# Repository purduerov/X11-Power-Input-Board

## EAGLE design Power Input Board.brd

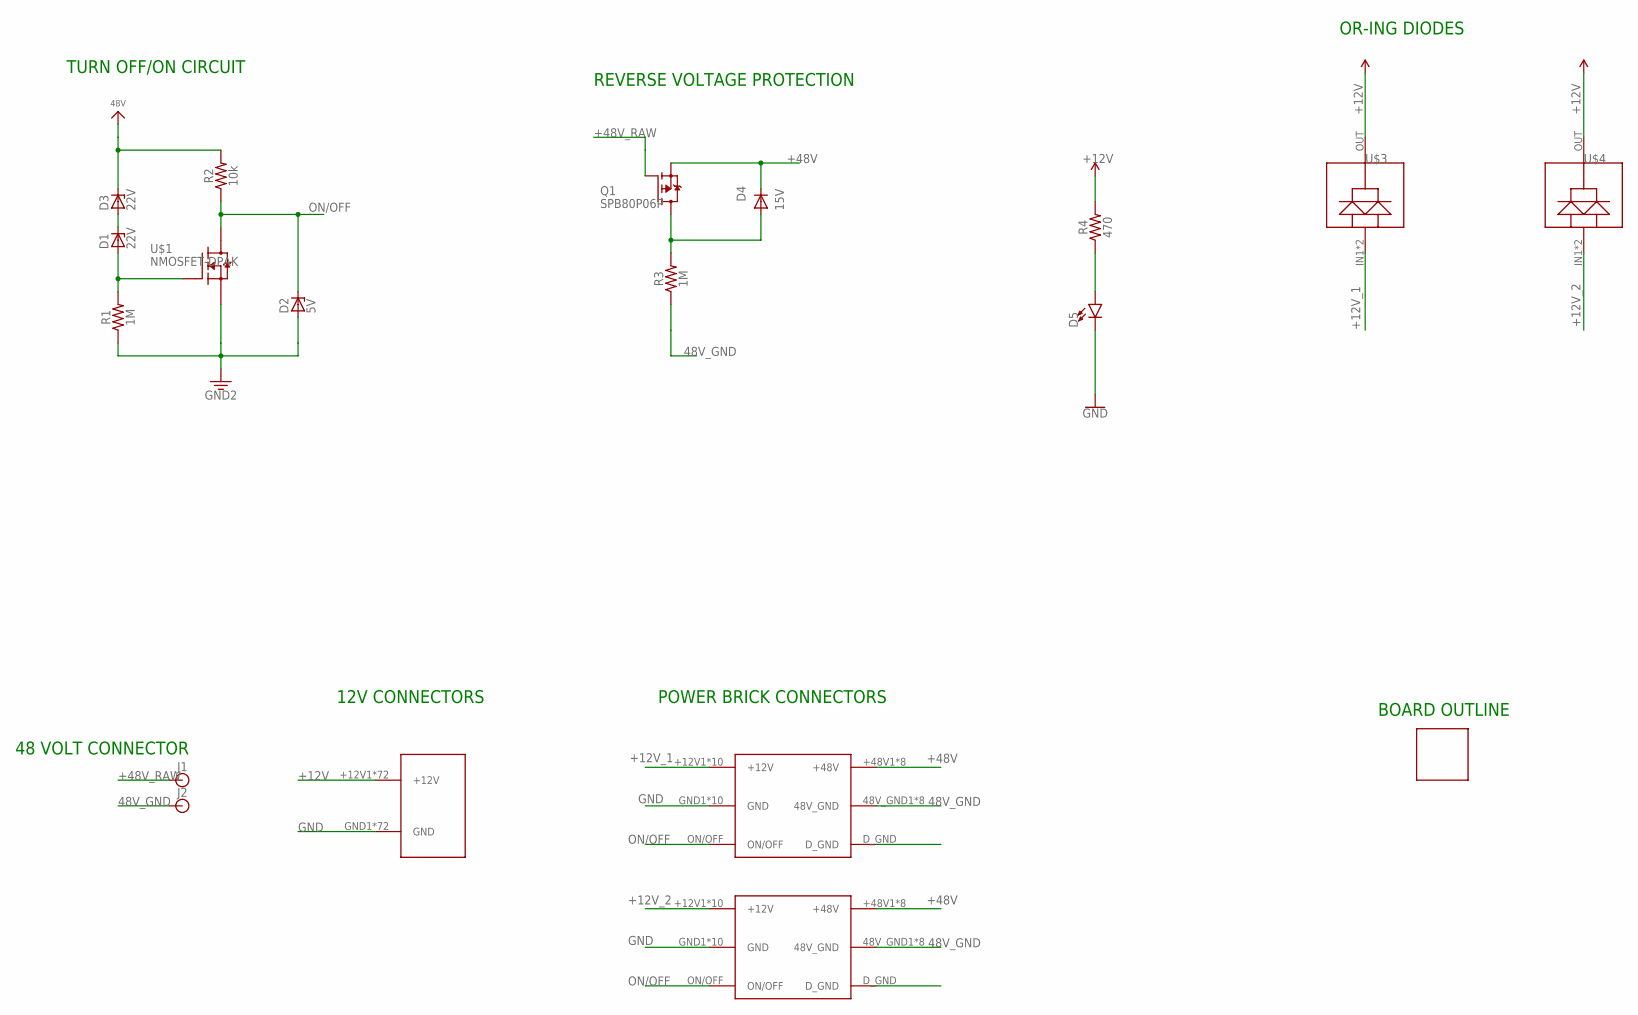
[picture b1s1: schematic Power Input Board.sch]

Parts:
D1, D3: 22V; SOT23
D2: 5V; SOT23
D4: 15V; SOD123
D5: LED0603; LED-0603
J1, J2: BANANA_CONN
Q1: SPB80P06P; TO263
R1, R3: 1M; 0603
R2: 10k; 0603
R4: 470; 0603
U$1: NMOSFET-DPAK; DPAK
U$2: BOARDPDB; PDB
U$3, U$4: DIODE
U$5, U$6: BRICK_TO_POWER_DIST_WHOLE
U$7: PDB_PCB_CONNEC; PDB_PCB_2

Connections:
3.3V: D2.1 (A), R1.1, U$1.3 (S)
48V_GND: J2.P$1, R3.1, U$5.48V_GND1 (48V_GND), U$5.48V_GND2 (48V_GND), U$5.48V_GND3 (48V_GND), U$5.48V_GND4 (48V_GND), U$5.48V_GND5 (48V_GND), U$5.48V_GND6 (48V_GND), U$5.48V_GND7 (48V_GND), U$5.48V_GND8 (48V_GND), U$6.48V_GND1 (48V_GND), U$6.48V_GND2 (48V_GND), U$6.48V_GND3 (48V_GND), U$6.48V_GND4 (48V_GND), U$6.48V_GND5 (48V_GND), U$6.48V_GND6 (48V_GND), U$6.48V_GND7 (48V_GND), U$6.48V_GND8 (48V_GND)
+12V: R4.2, U$3.OUT, U$4.OUT, U$7.+12V1 (+12V), U$7.+12V2 (+12V), U$7.+12V3 (+12V), U$7.+12V4 (+12V), U$7.+12V5 (+12V), U$7.+12V6 (+12V), U$7.+12V7 (+12V), U$7.+12V8 (+12V), U$7.+12V9 (+12V), U$7.+12V10 (+12V), U$7.+12V11 (+12V), U$7.+12V12 (+12V), U$7.+12V13 (+12V), U$7.+12V14 (+12V), U$7.+12V15 (+12V), U$7.+12V16 (+12V), U$7.+12V17 (+12V), U$7.+12V18 (+12V), U$7.+12V19 (+12V), U$7.+12V20 (+12V), U$7.+12V21 (+12V), U$7.+12V22 (+12V), U$7.+12V23 (+12V), U$7.+12V24 (+12V), U$7.+12V25 (+12V), U$7.+12V26 (+12V), U$7.+12V27 (+12V), U$7.+12V28 (+12V), U$7.+12V29 (+12V), U$7.+12V30 (+12V), U$7.+12V31 (+12V), U$7.+12V32 (+12V), U$7.+12V33 (+12V), U$7.+12V34 (+12V), U$7.+12V35 (+12V), U$7.+12V36 (+12V), U$7.+12V37 (+12V), U$7.+12V38 (+12V), U$7.+12V39 (+12V), U$7.+12V40 (+12V), U$7.+12V41 (+12V), U$7.+12V42 (+12V), U$7.+12V43 (+12V), U$7.+12V44 (+12V), U$7.+12V45 (+12V), U$7.+12V46 (+12V), U$7.+12V47 (+12V), U$7.+12V48 (+12V), U$7.+12V49 (+12V), U$7.+12V50 (+12V), U$7.+12V51 (+12V), U$7.+12V52 (+12V), U$7.+12V53 (+12V), U$7.+12V54 (+12V), U$7.+12V55 (+12V), U$7.+12V56 (+12V), U$7.+12V57 (+12V), U$7.+12V58 (+12V), U$7.+12V59 (+12V), U$7.+12V60 (+12V), U$7.+12V61 (+12V), U$7.+12V62 (+12V), U$7.+12V63 (+12V), U$7.+12V64 (+12V), U$7.+12V65 (+12V), U$7.+12V66 (+12V), U$7.+12V67 (+12V), U$7.+12V68 (+12V), U$7.+12V69 (+12V), U$7.+12V70 (+12V), U$7.+12V71 (+12V), U$7.+12V72 (+12V)
+12V_1: U$3.IN1 (IN2), U$3.IN2, U$5.+12V1 (+12V), U$5.+12V2 (+12V), U$5.+12V3 (+12V), U$5.+12V4 (+12V), U$5.+12V5 (+12V), U$5.+12V6 (+12V), U$5.+12V7 (+12V), U$5.+12V8 (+12V), U$5.+12V9 (+12V), U$5.+12V10 (+12V)
+12V_2: U$4.IN1 (IN2), U$4.IN2, U$6.+12V1 (+12V), U$6.+12V2 (+12V), U$6.+12V3 (+12V), U$6.+12V4 (+12V), U$6.+12V5 (+12V), U$6.+12V6 (+12V), U$6.+12V7 (+12V), U$6.+12V8 (+12V), U$6.+12V9 (+12V), U$6.+12V10 (+12V)
+48V: D4.C, Q1.2 (S), U$5.+48V1 (+48V), U$5.+48V2 (+48V), U$5.+48V3 (+48V), U$5.+48V4 (+48V), U$5.+48V5 (+48V), U$5.+48V6 (+48V), U$5.+48V7 (+48V), U$5.+48V8 (+48V), U$6.+48V1 (+48V), U$6.+48V2 (+48V), U$6.+48V3 (+48V), U$6.+48V4 (+48V), U$6.+48V5 (+48V), U$6.+48V6 (+48V), U$6.+48V7 (+48V), U$6.+48V8 (+48V)
+48V_RAW: J1.P$1, Q1.1 (G)
GND: D5.C, U$5.GND1 (GND), U$5.GND2 (GND), U$5.GND3 (GND), U$5.GND4 (GND), U$5.GND5 (GND), U$5.GND6 (GND), U$5.GND7 (GND), U$5.GND8 (GND), U$5.GND9 (GND), U$5.GND10 (GND), U$6.GND1 (GND), U$6.GND2 (GND), U$6.GND3 (GND), U$6.GND4 (GND), U$6.GND5 (GND), U$6.GND6 (GND), U$6.GND7 (GND), U$6.GND8 (GND), U$6.GND9 (GND), U$6.GND10 (GND), U$7.GND1 (GND), U$7.GND2 (GND), U$7.GND3 (GND), U$7.GND4 (GND), U$7.GND5 (GND), U$7.GND6 (GND), U$7.GND7 (GND), U$7.GND8 (GND), U$7.GND9 (GND), U$7.GND10 (GND), U$7.GND11 (GND), U$7.GND12 (GND), U$7.GND13 (GND), U$7.GND14 (GND), U$7.GND15 (GND), U$7.GND16 (GND), U$7.GND17 (GND), U$7.GND18 (GND), U$7.GND19 (GND), U$7.GND20 (GND), U$7.GND21 (GND), U$7.GND22 (GND), U$7.GND23 (GND), U$7.GND24 (GND), U$7.GND25 (GND), U$7.GND26 (GND), U$7.GND27 (GND), U$7.GND28 (GND), U$7.GND29 (GND), U$7.GND30 (GND), U$7.GND31 (GND), U$7.GND32 (GND), U$7.GND33 (GND), U$7.GND34 (GND), U$7.GND35 (GND), U$7.GND36 (GND), U$7.GND37 (GND), U$7.GND38 (GND), U$7.GND39 (GND), U$7.GND40 (GND), U$7.GND41 (GND), U$7.GND42 (GND), U$7.GND43 (GND), U$7.GND44 (GND), U$7.GND45 (GND), U$7.GND46 (GND), U$7.GND47 (GND), U$7.GND48 (GND), U$7.GND49 (GND), U$7.GND50 (GND), U$7.GND51 (GND), U$7.GND52 (GND), U$7.GND53 (GND), U$7.GND54 (GND), U$7.GND55 (GND), U$7.GND56 (GND), U$7.GND57 (GND), U$7.GND58 (GND), U$7.GND59 (GND), U$7.GND60 (GND), U$7.GND61 (GND), U$7.GND62 (GND), U$7.GND63 (GND), U$7.GND64 (GND), U$7.GND65 (GND), U$7.GND66 (GND), U$7.GND67 (GND), U$7.GND68 (GND), U$7.GND69 (GND), U$7.GND70 (GND), U$7.GND71 (GND), U$7.GND72 (GND)
unnamed: D1.3 (C), D3.1 (A)
unnamed: D1.1 (A), R1.2, U$1.1 (G)
unnamed: D4.A, Q1.3 (D), R3.2
unnamed: D5.A, R4.1
unnamed: D3.3 (C), R2.2
ON/OFF: D2.3 (C), R2.1, U$1.4 (D1), U$5.ON/OFF, U$6.ON/OFF

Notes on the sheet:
48 VOLT CONNECTOR
12V CONNECTORS
POWER BRICK CONNECTORS
TURN OFF/ON CIRCUIT
REVERSE VOLTAGE PROTECTION
BOARD OUTLINE
OR-ING DIODES

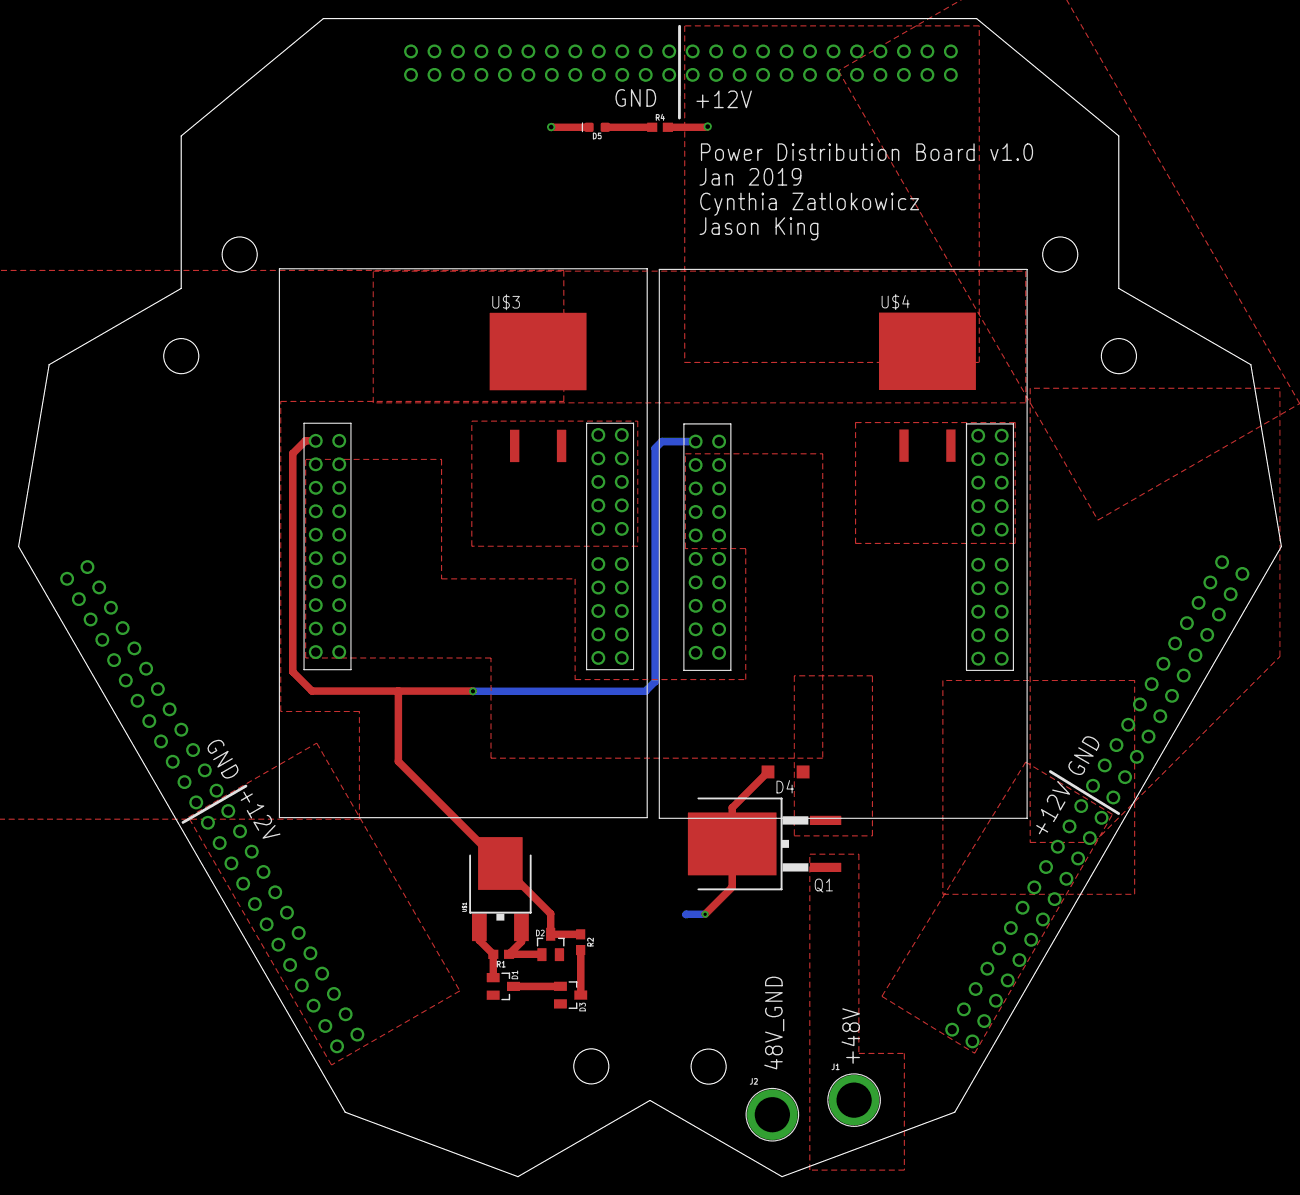
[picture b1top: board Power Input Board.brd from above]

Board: 2 copper layers, 136.7 x 125.3 mm, 19 parts (1 on the bottom side), 14 nets.

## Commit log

2018-09-19 added gitignore
2018-10-17 added board outline
    added the board outline
2018-11-03 put in outline
2018-11-09 added brick outlines
2018-11-09 inserted diodes
2018-11-10 put the connectors on the board
2018-11-10 reconstructing
2018-11-10 added connectors
2018-11-10 routed roughly
2018-11-10 fixed airwire
2018-11-15 took off the dumb lines
    took off the routed lines that wouldve popped off the board
2018-11-30 fixed some stuff
    moved things around
2018-12-07 rerouted
    repositioned the polygons and rerouted the components
2018-12-15 rerouted
    rerouted the whole board
2018-12-28 rerouted
    rerouted everything
2018-12-30 Added some silkscreen
2018-12-30 fixed things and put silkscreen symbol
2018-12-30 created symbol
2018-12-31 added LED
    added LED between 12V and GND
2019-01-02 repositioning components
2019-01-03 small moves
2019-01-12 i didnt update but ok
2019-01-12 Fixing DS store

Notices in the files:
parts and their libraries:
SparkFun-Resistors: Licensing: Creative Commons ShareAlike 4.0 International - https://creativecommons.org/licenses/by-sa/4.0
